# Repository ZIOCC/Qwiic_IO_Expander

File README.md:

# Qwiic IO Expander

> This product can be available for purchase [here](https://www.smart-prototyping.com/Zio-Qwiic-IO-Expander.html).

#### Description

Running out of GPIO pins on the MCU controlling your Qwiic-based project? Add 16 extra, fully programmable GPIO pins with the Zio Qwiic I/O Expander. 

Another useful feature of this board is its ability to produce PWM signals enabling control of LEDs or any other PWM controllable device with a maximum 15mA output sink current.

The board is laid out so that it’s easy to solder components directly to it or for more flexible prototyping, solder on some header pins and drop in a breadboard. 

All I/O pins are 5.5V tolerant but we recommend voltages between 1.2-3.6V for optimal operation. The board has a 400kHz I2C compatible slave interface fast enough for most high-speed demanding projects and features an on-chip keypad scanning engine supporting up to 64 keys in an 8x8 matrix.

The I/O Expander features two Qwiic connectors for quick and easy daisy-chaining with other Qwiic-compatible I2C boards. 

> This PCB is a derivative of [Sparkfun's SX1509 IO-Expander](https://github.com/sparkfun/SX1509_IO-Expander), and can be used with their [Arduino library](https://github.com/sparkfun/SparkFun_SX1509_Arduino_Library).

> Note: As with all of the Version 1.0 Zio Qwiic boards, this board has been produced with the I2C pull-ups disconnected by default. If there's a significant length of wire between this board and your MCU, you'll need to solder closed the solder jumpers (labeled SDA, 3v3 and SCL) to connect the pull-up resistors to VCC.

##### Features

* Semtech SX1509
* 16 I/O Channels
* 1.2V to 3.6V low operating voltage.
* 5.5V Tolerant I/O up to 15mA output sink current on all I/Os.
* 2 Qwiic connectors
* 4 User selectable I2C compatible slave interface.
* PWM Intensity control (256-step PWM)

#### Specification

* Ultra-low current consumption of typically 1uA.
* -40°C to +85°C Operating Temperature Range
* 400kHz I2C compatible slave interface
* Blink and breathing control (224 On/Off values for each)
* Open drain active low interrupt output (NINT)
* Direct level shifting between I/O banks and host controller.
* IC: SX1509
* I2C address: 0x3E, 0x3F, 0x70, 0x71 (Default: 0x3E)
* Dimensions (LxWxH) 33x18mm
* Weight: 1.5g (0.06oz)

#### Links

* [SX1509 Datasheet](https://www.smart-prototyping.com/image/data/NOA-RnD/101901%20IO%20Expander/sx150x_89b.pdf)
* [SparkFun SX1509 Arduino Library](https://github.com/sparkfun/SparkFun_SX1509_Arduino_Library)
* [Eagle files](https://github.com/ZIOCC/Qwiic_IO_Expander)

> ###### About Zio
> Zio is a new line of open sourced, compact, and grid layout boards, fully integrated for Arduino and Qwiic ecosystem. Designed ideally for wearables, robotics, small-space limitations or other on the go projects. Check out other awesome Zio products [here](https://www.smart-prototyping.com/Zio).

> All Zio products are released under the [Creative Commons Attribution, Share-Alike License](https://creativecommons.org/licenses/by-sa/4.0/), and in accordance with the principles of the [Open Source Hardware Association's OSHW Statement of Principles 1.0 and OSHW Definition 1.0](https://www.oshwa.org/definition/).

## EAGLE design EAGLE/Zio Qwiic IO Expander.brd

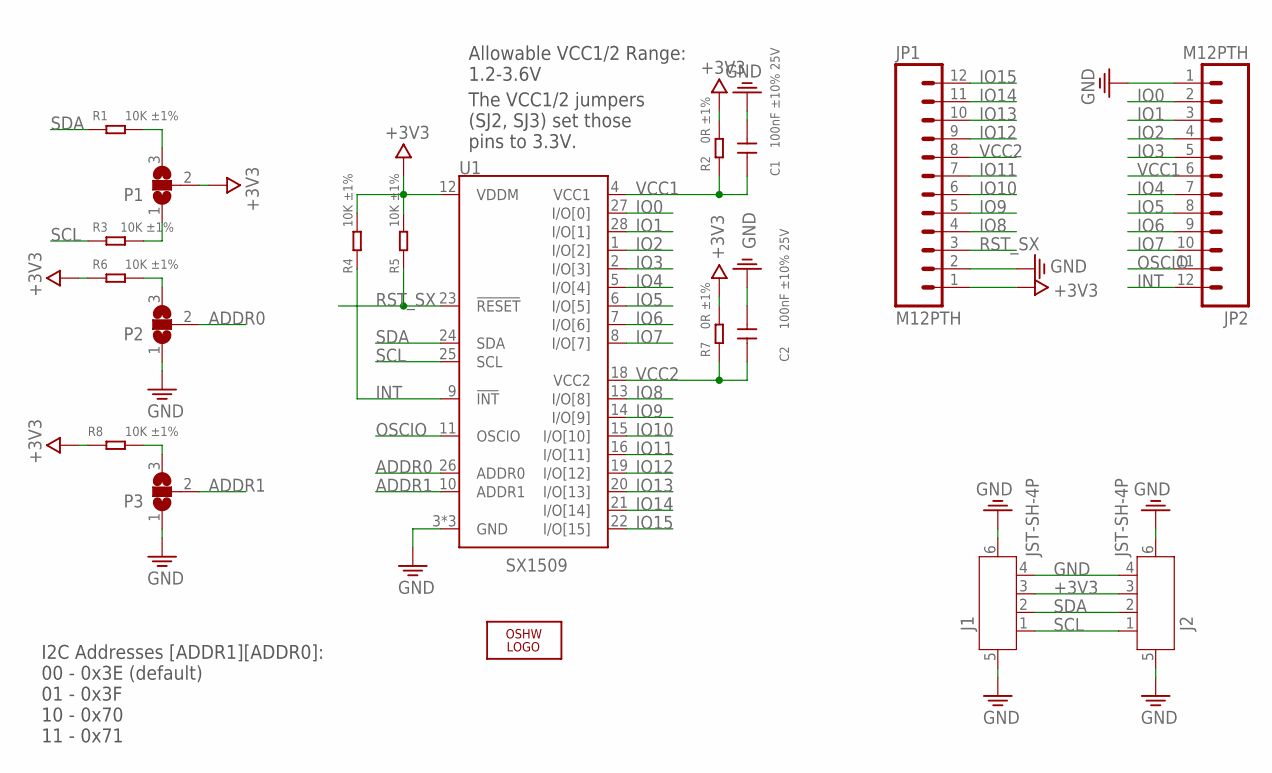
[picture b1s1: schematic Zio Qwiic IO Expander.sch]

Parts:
C1, C2: 100nF ±10% 25V; 0402
J1, J2: JST-SH-4P; JST-SH-4P-90
JP1, JP2: M12PTH; 1X12
LOGO: LOGO-OSHW-6MILX0100-NT; OSHW_6X100_NOTEXT
P1, P2, P3: PAD-SOLDERJUMPER-2WAY; 3P-SMD-1.78X1.27
R1, R3, R4, R5, R6, R8: 10K ±1%; 0402
R2, R7: 0R ±1%; 0402
U1: SX1509; QFN-28

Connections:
+3V3: J1.3, J2.3, JP1.1, P1.2, R2.2, R4.2, R5.2, R6.1, R7.2, R8.1, U1.12 (VDDM)
ADDR0: P2.2, U1.26 (ADDR0)
ADDR1: P3.2, U1.10 (ADDR1)
GND: C1.2, C2.2, J1.4, J1.5, J1.6, J2.4, J2.5, J2.6, JP1.2, JP2.1, P2.1, P3.1, U1.3 (GND), U1.17 (GND), U1.29 (GND)
INT: JP2.12, R4.1, U1.9 (!INT)
IO0: JP2.2, U1.27 (I/O[0])
IO1: JP2.3, U1.28 (I/O[1])
IO2: JP2.4, U1.1 (I/O[2])
IO3: JP2.5, U1.2 (I/O[3])
IO4: JP2.7, U1.5 (I/O[4])
IO5: JP2.8, U1.6 (I/O[5])
IO6: JP2.9, U1.7 (I/O[6])
IO7: JP2.10, U1.8 (I/O[7])
IO8: JP1.4, U1.13 (I/O[8])
IO9: JP1.5, U1.14 (I/O[9])
IO10: JP1.6, U1.15 (I/O[10])
IO11: JP1.7, U1.16 (I/O[11])
IO12: JP1.9, U1.19 (I/O[12])
IO13: JP1.10, U1.20 (I/O[13])
IO14: JP1.11, U1.21 (I/O[14])
IO15: JP1.12, U1.22 (I/O[15])
unnamed: P1.3, R1.2
unnamed: P1.1, R3.2
unnamed: P2.3, R6.2
unnamed: P3.3, R8.2
OSCIO: JP2.11, U1.11 (OSCIO)
RST_SX: JP1.3, R5.1, U1.23 (!RESET)
SCL: J1.1, J2.1, R3.1, U1.25 (SCL)
SDA: J1.2, J2.2, R1.1, U1.24 (SDA)
VCC1: C1.1, JP2.6, R2.1, U1.4 (VCC1)
VCC2: C2.1, JP1.8, R7.1, U1.18 (VCC2)

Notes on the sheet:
The VCC1/2 jumpers (SJ2, SJ3) set those pins to 3.3V.
Allowable VCC1/2 Range: 1.2-3.6V
I2C Addresses [ADDR1][ADDR0]: 00 - 0x3E (default) 01 - 0x3F 10 - 0x70 11 - 0x71

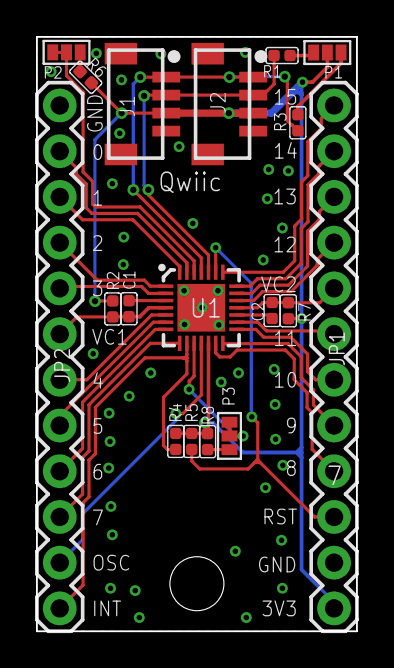
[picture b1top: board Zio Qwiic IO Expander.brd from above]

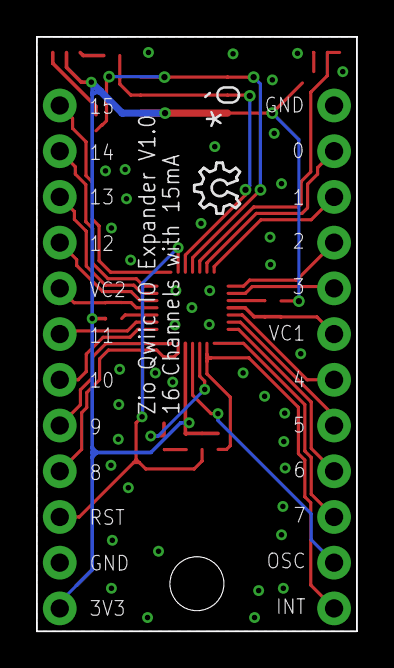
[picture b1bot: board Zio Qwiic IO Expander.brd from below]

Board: 2 copper layers, 17.8 x 33.0 mm, 21 parts (2 on the bottom side), 31 nets.

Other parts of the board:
E$3: 6MM
U$7: 6MM
